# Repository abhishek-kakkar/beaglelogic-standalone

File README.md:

# beaglelogic-standalone

BeagleLogic implemented as a turnkey and standalone logic analyzer

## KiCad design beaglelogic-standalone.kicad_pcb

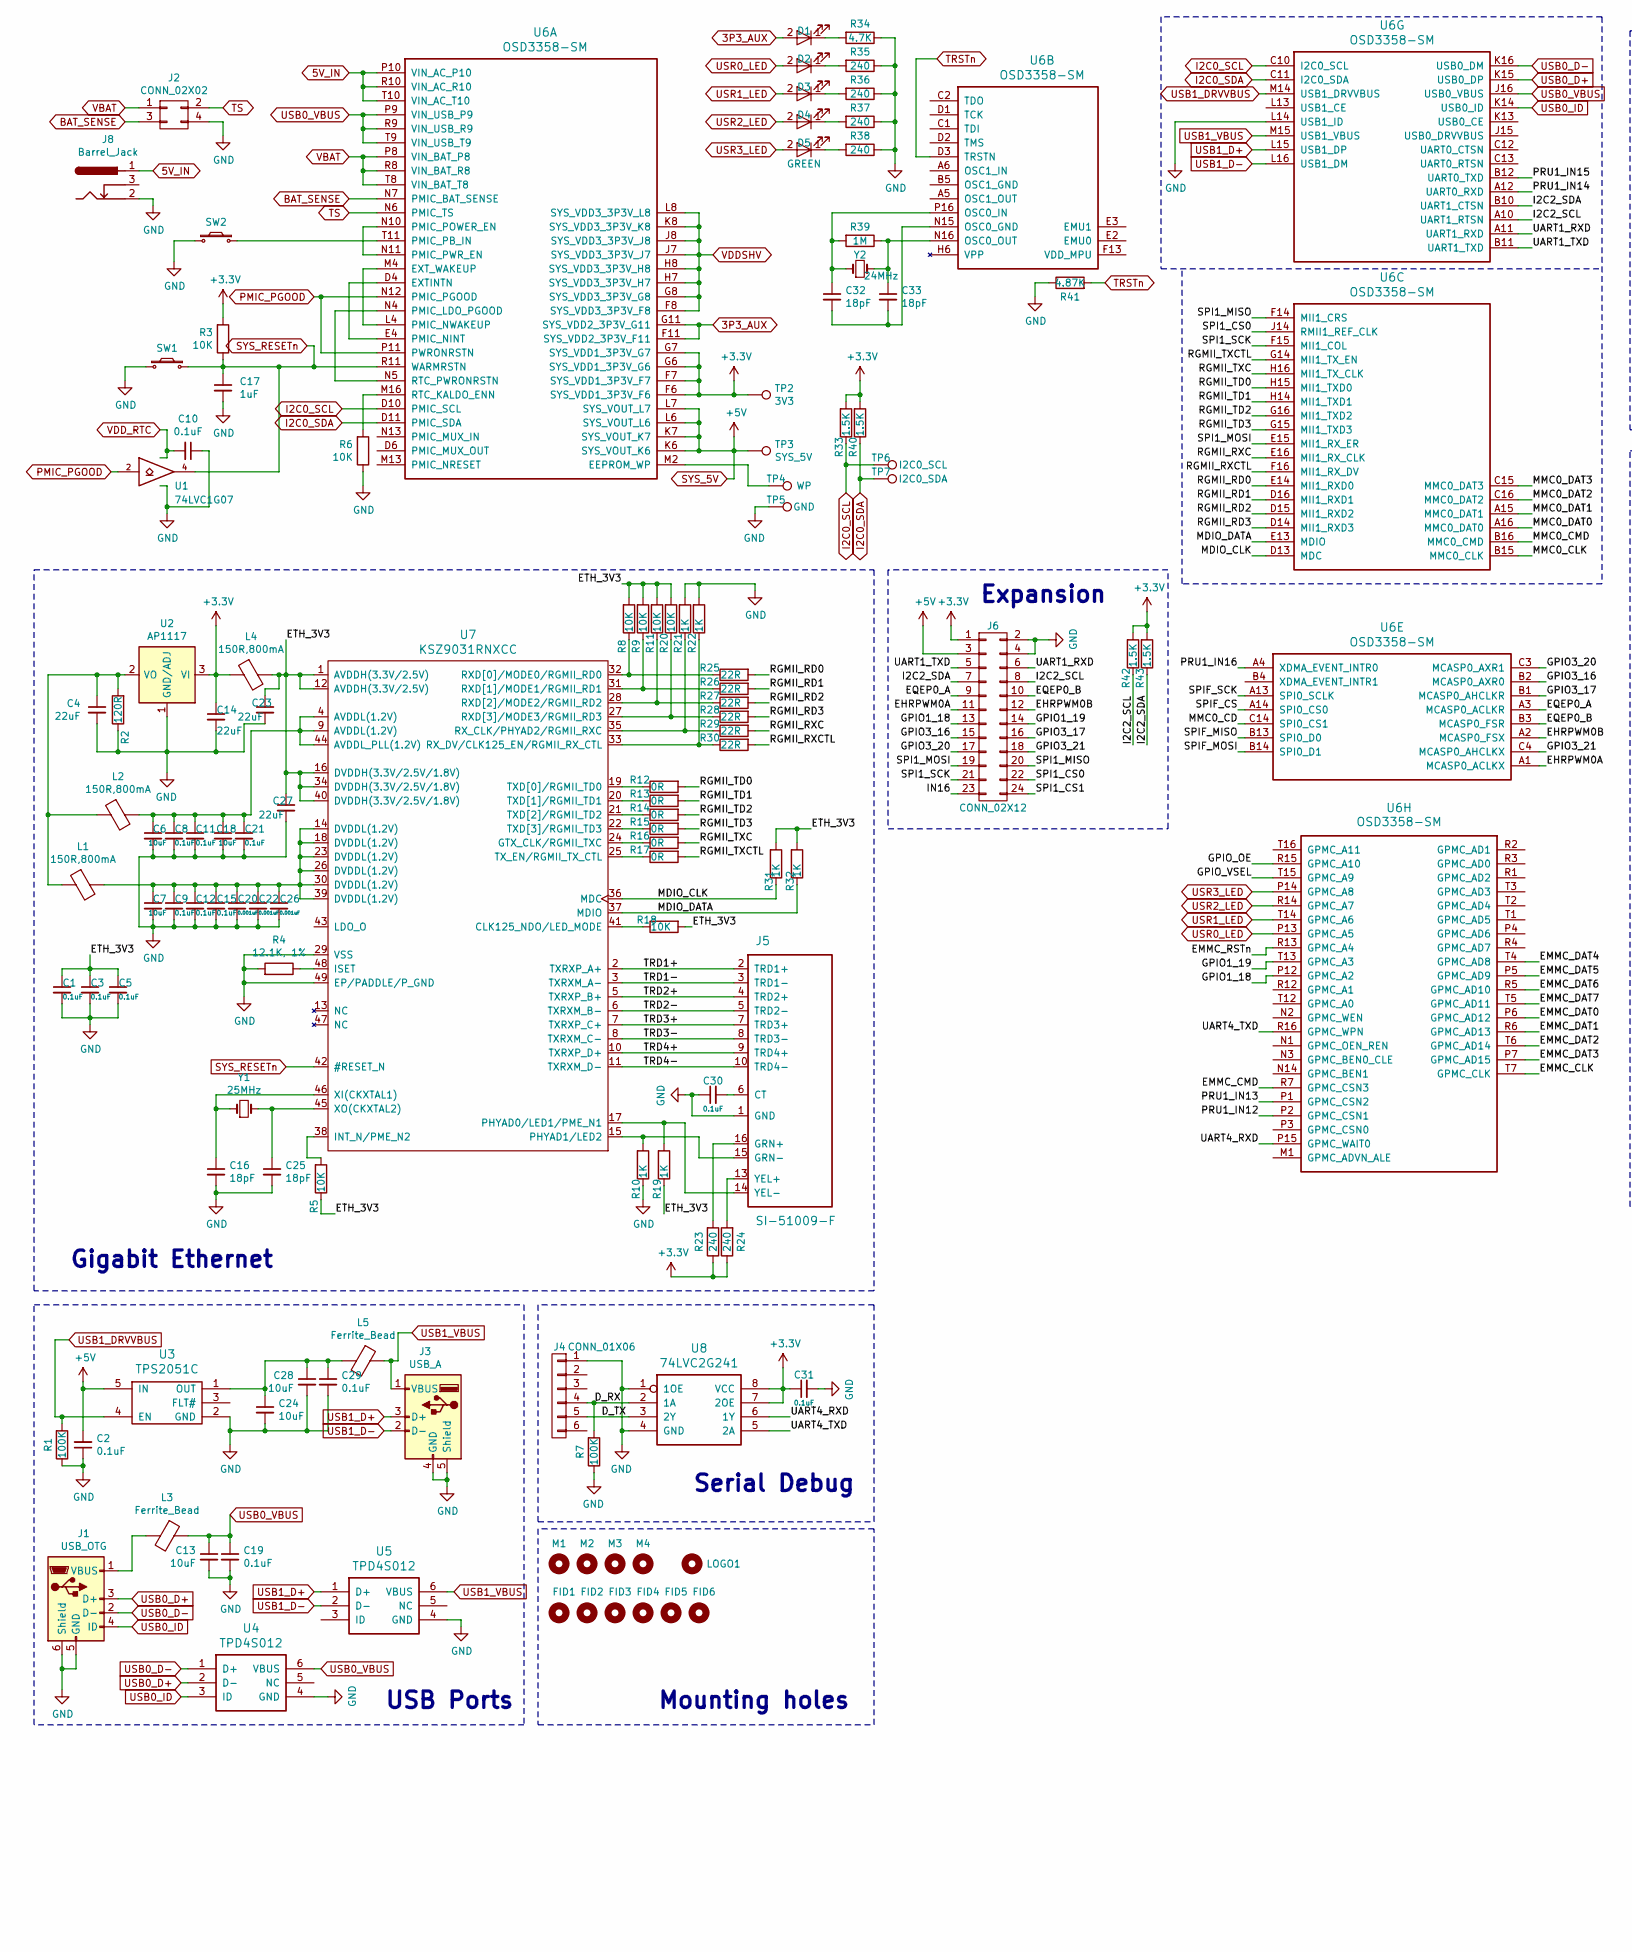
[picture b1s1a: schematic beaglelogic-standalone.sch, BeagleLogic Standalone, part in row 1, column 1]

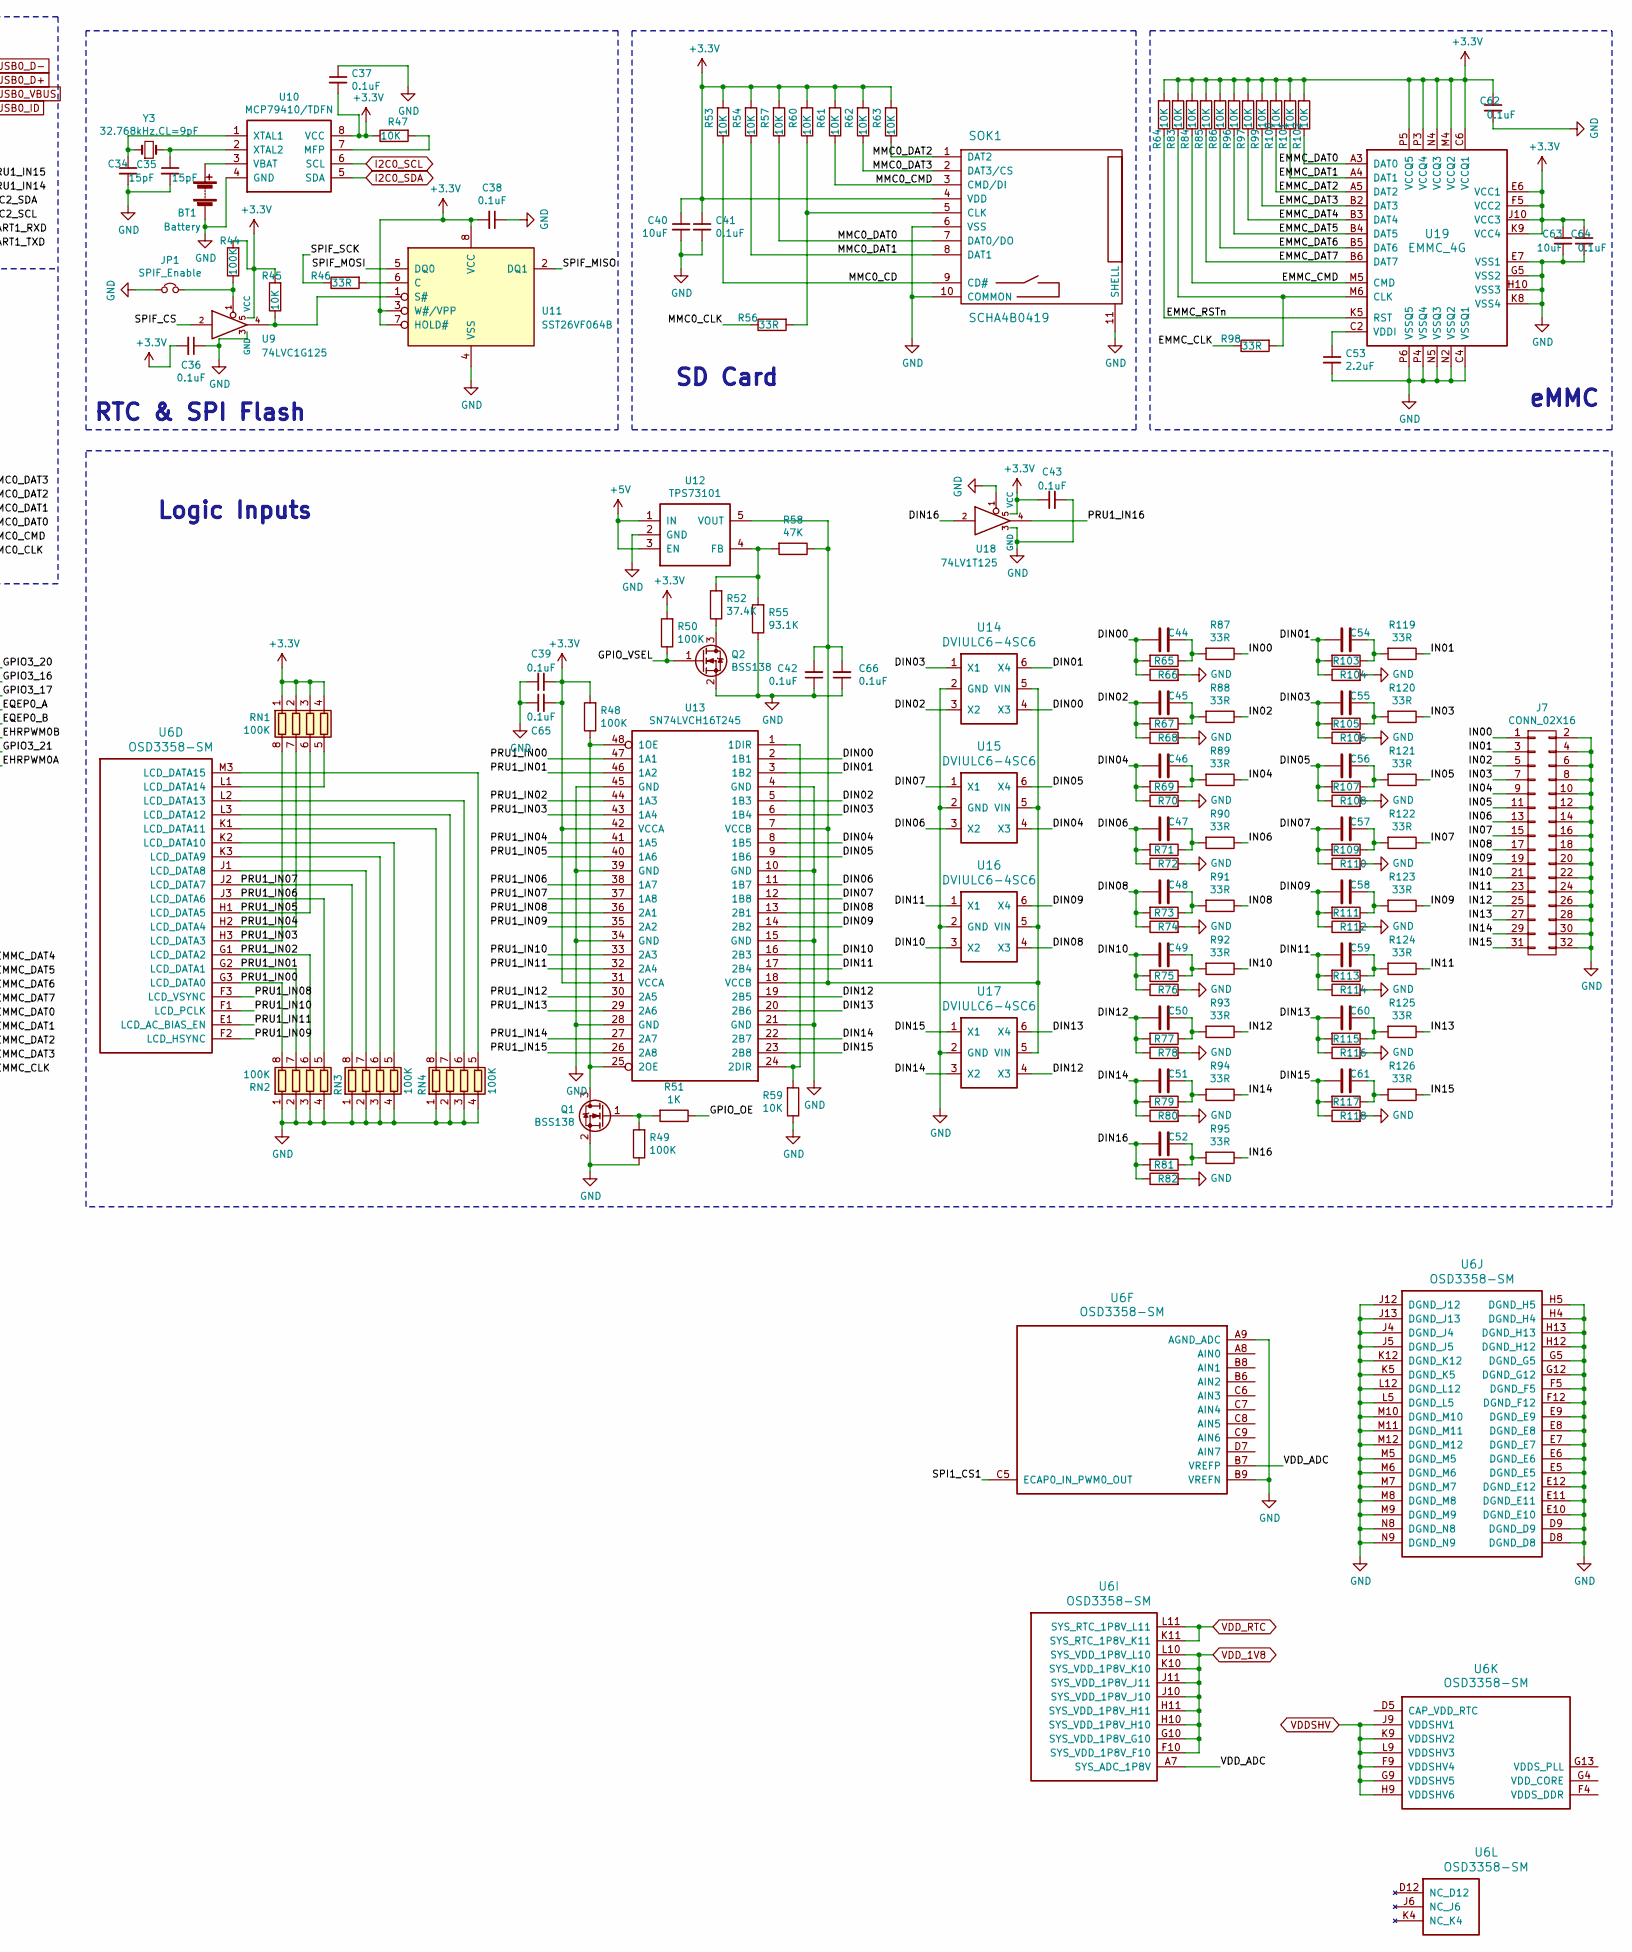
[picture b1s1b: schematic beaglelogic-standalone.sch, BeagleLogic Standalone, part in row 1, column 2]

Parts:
BT1: Battery; Test_Point_2Pads
C1, C2, C3, C5, C8, C9, C10, C11, C12, C15, C19, C21, C29, C30, C31, C36, C37, C38, C39, C41, C42, C43, C62, C64, C65, C66: 0.1uF; C_0402
C4, C14, C23, C27: 22uF; C_0603
C6, C7, C13, C18, C24, C28, C40, C63: 10uF; C_0603
C16, C25, C32, C33: 18pF; C_0402
C17: 1uF; C_0402
C20, C22, C26: 0.001uF; C_0402
C34, C35: 15pF; C_0402
C44, C45, C46, C47, C48, C49, C50, C51, C52, C54, C55, C56, C57, C58, C59, C60, C61: 1pF, DNI; C_0402
C53: 2.2uF; C_0402
D1, D2, D3, D4, D5: GREEN; LED_0603
FID1, FID2, FID3, FID4, FID5, FID6: Mounting_Hole; Fiducial_1mm_Dia_2.54mm_Outer_CopperTop
J1: USB_OTG; 10118192-0001LF
J2: CONN_02X02; Pin_Header_Straight_2x02_Pitch2.54mm
J3: USB_A
J4: CONN_01X06; Pin_Header_Straight_1x06_Pitch2.54mm
J5: SI-51009-F
J6: CONN_02X12; Pin_Header_Angled_2x12_Pitch2.54mm_reversed
J7: CONN_02X16; Pin_Header_Angled_2x16_Pitch2.54mm
J8: Barrel_Jack; BARREL_JACK
JP1: SPIF_Enable; Test_Point_2Pads
L1, L2, L4: 150R,800mA; R_0603
L3, L5: Ferrite_Bead; R_0603
LOGO1: TEST_1P; beaglelogic-logo
M1, M2, M3, M4: TEST_1P; MountingHole_3.2mm_M3
Q1, Q2: BSS138; SOT-23
R1, R7, R44, R48, R49, R50: 100K; R_0402
R2: 120R; R_0603
R3, R5, R6, R8, R9, R11, R18, R20, R45, R47, R53, R54, R57, R59, R60, R61, R62, R63, R64, R83, R84, R85, R86, R96, R97, R99, R100, R101, R102: 10K; R_0402
R4: 12.1K, 1%; R_0402
R10, R19, R21, R22, R31, R32, R51: 1K; R_0402
R12, R13, R14, R15, R16, R17: 0R; R_0402
R23, R24, R35, R36, R37, R38: 240; R_0402
R25, R26, R27, R28, R29, R30: 22R; R_0402
R33, R40, R42, R43: 1.5K; R_0402
R34: 4.7K; R_0402
R39: 1M; R_0402
R41: 4.87K; R_0402
R46, R56, R87, R88, R89, R90, R91, R92, R93, R94, R95, R98, R119, R120, R121, R122, R123, R124, R125, R126: 33R; R_0402
R52: 37.4K; R_0402
R55: 93.1K; R_0402
R58: 47K; R_0402
R65, R67, R69, R71, R73, R75, R77, R79, R81, R103, R105, R107, R109, R111, R113, R115, R117: 100K,SH; R_0402
R66, R68, R70, R72, R74, R76, R78, R80, R82, R104, R106, R108, R110, R112, R114, R116, R118: 1M,S; R_0402
RN1, RN2, RN3, RN4: 100K; R_Array_Concave_4x0402
SOK1: SCHA4B0419
SW1, SW2: SW_PUSH_SMALL_H; SW_SPST_EVQPE1
TP2: 3V3; Measurement_Point_Round-SMD-Pad_Small
TP3: SYS_5V; Measurement_Point_Round-SMD-Pad_Small
TP4: WP; Measurement_Point_Round-SMD-Pad_Small
TP5: GND; Measurement_Point_Round-SMD-Pad_Small
TP6: I2C0_SCL; Measurement_Point_Round-SMD-Pad_Small
TP7: I2C0_SDA; Measurement_Point_Round-SMD-Pad_Small
U1: 74LVC1G07; SOT-353_SC-70-5
U2: AP1117; SOT-223
U3: TPS2051C; SOT-23-5
U4, U5: TPD4S012; DRY
U6: OSD3358-SM; BGA-256-1-27mm
U7: KSZ9031RNXCC; QFN-48-1EP_7x7mm
U8: 74LVC2G241; VSSOP-8_2.4x2.1mm_Pitch0.5mm
U9: 74LVC1G125; SOT-353_SC-70-5
U10: MCP79410/TDFN; DFN-8-1EP_3x2mm
U11: SST26VF064B; SOIJ-8_5.3x5.3mm_Pitch1.27mm
U12: TPS73101; SOT-23-5
U13: SN74LVCH16T245; TSSOP-48_6.1x12.5mm_Pitch0.5mm
U14, U15, U16, U17: DVIULC6-4SC6; SOT-23-6
U18: 74LV1T125; SOT-353_SC-70-5
U19: EMMC_4G; BGA153N50P14X14_1150X1300X100
Y1: 25MHz; Crystal_SMD_5032-2pin_5.0x3.2mm
Y2: 24MHz; Crystal_SMD_5032-2pin_5.0x3.2mm
Y3: 32.768kHz,CL=9pF; Crystal_SMD_3215-2pin_3.2x1.5mm

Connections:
3P3_AUX: D1.2 (A), U6.F11 (SYS_VDD2_3P3V_F11), U6.G11 (SYS_VDD2_3P3V_G11)
5V_IN: J8.1, U6.P10 (VIN_AC_P10), U6.R10 (VIN_AC_R10), U6.T10 (VIN_AC_T10)
+3V3: C14.1, C31.1, C36.2, C37.2, C38.2, C39.2, C40.1, C41.1, C43.1, C62.1, C63.1, C64.1, C65.2, J6.1, L4.1, R3.2, R23.1, R24.1, R33.2, R40.2, R42.2, R43.2, R44.2, R45.2, R47.1, R48.2, R50.2, R53.2, R54.2, R57.2, R60.2, R61.2, R62.2, R63.2, R64.2, R83.2, R84.2, R85.2, R86.2, R96.2, R97.2, R99.2, R100.2, R101.2, R102.2, RN1.1 (R1.1), RN1.2 (R2.1), RN1.3 (R3.1), RN1.4 (R4.1), SOK1.4 (VDD), TP2.1, U2.3 (VI), U6.F6 (SYS_VDD1_3P3V_F6), U6.F7 (SYS_VDD1_3P3V_F7), U6.G6 (SYS_VDD1_3P3V_G6), U6.G7 (SYS_VDD1_3P3V_G7), U8.7 (2OE), U8.8 (VCC), U9.5 (VCC), U10.8 (VCC), U11.3 (W#/VPP), U11.7 (HOLD#), U11.8 (VCC), U13.31 (VCCA), U13.42 (VCCA), U18.5 (VCC), U19.C6 (VCCQ1), U19.E6 (VCC1), U19.F5 (VCC2), U19.J10 (VCC3), U19.K9 (VCC4), U19.M4 (VCCQ2), U19.N4 (VCCQ3), U19.P3 (VCCQ4), U19.P5 (VCCQ5)
/DIN00: C44.2, R65.2, R66.1, U13.2 (1B1), U14.4 (X3)
/DIN01: C54.2, R103.2, R104.1, U13.3 (1B2), U14.6 (X4)
/DIN02: C45.2, R67.2, R68.1, U13.5 (1B3), U14.3 (X2)
/DIN03: C55.2, R105.2, R106.1, U13.6 (1B4), U14.1 (X1)
/DIN04: C46.2, R69.2, R70.1, U13.8 (1B5), U15.4 (X3)
/DIN05: C56.2, R107.2, R108.1, U13.9 (1B6), U15.6 (X4)
/DIN06: C47.2, R71.2, R72.1, U13.11 (1B7), U15.3 (X2)
/DIN07: C57.2, R109.2, R110.1, U13.12 (1B8), U15.1 (X1)
/DIN08: C48.2, R73.2, R74.1, U13.13 (2B1), U16.4 (X3)
/DIN09: C58.2, R111.2, R112.1, U13.14 (2B2), U16.6 (X4)
/DIN10: C49.2, R75.2, R76.1, U13.16 (2B3), U16.3 (X2)
/DIN11: C59.2, R113.2, R114.1, U13.17 (2B4), U16.1 (X1)
/DIN12: C50.2, R77.2, R78.1, U13.19 (2B5), U17.4 (X3)
/DIN13: C60.2, R115.2, R116.1, U13.20 (2B6), U17.6 (X4)
/DIN14: C51.2, R79.2, R80.1, U13.22 (2B7), U17.3 (X2)
/DIN15: C61.2, R117.2, R118.1, U13.23 (2B8), U17.1 (X1)
/DIN16: C52.2, R81.2, R82.1, U18.2
/D_RX: J4.4, R7.2, U8.2 (1A)
/D_TX: J4.5, U8.3 (2Y)
/EHRPWM0A: J6.11, U6.A1 (MCASP0_ACLKX)
/EHRPWM0B: J6.12, U6.A2 (MCASP0_FSX)
/EMMC_CLK: R98.1, U6.T7 (GPMC_CLK)
/EMMC_CMD: R84.1, U6.R7 (GPMC_CSN3), U19.M5 (CMD)
/EMMC_DAT0: R102.1, U6.P6 (GPMC_AD12), U19.A3 (DAT0)
/EMMC_DAT1: R101.1, U6.R6 (GPMC_AD13), U19.A4 (DAT1)
/EMMC_DAT2: R100.1, U6.T6 (GPMC_AD14), U19.A5 (DAT2)
/EMMC_DAT3: R99.1, U6.P7 (GPMC_AD15), U19.B2 (DAT3)
/EMMC_DAT4: R97.1, U6.T4 (GPMC_AD8), U19.B3 (DAT4)
/EMMC_DAT5: R96.1, U6.P5 (GPMC_AD9), U19.B4 (DAT5)
/EMMC_DAT6: R86.1, U6.R5 (GPMC_AD10), U19.B5 (DAT6)
/EMMC_DAT7: R85.1, U6.T5 (GPMC_AD11), U19.B6 (DAT7)
/EMMC_RSTn: R64.1, U6.R13 (GPMC_A4), U19.K5 (RST)
/EQEP0_A: J6.9, U6.A3 (MCASP0_ACLKR)
/EQEP0_B: J6.10, U6.B3 (MCASP0_FSR)
/ETH_3V3: C1.1, C3.1, C5.1, C23.1, C27.1, L4.2, R5.1, R8.2, R9.2, R11.2, R18.2, R19.1, R20.2, R31.2, R32.2, U7.1 (AVDDH(3.3V/2.5V)), U7.12 (AVDDH(3.3V/2.5V)), U7.16 (DVDDH(3.3V/2.5V/1.8V)), U7.34 (DVDDH(3.3V/2.5V/1.8V)), U7.40 (DVDDH(3.3V/2.5V/1.8V))
/GPIO1_18: J6.13, U6.P12 (GPMC_A2)
/GPIO1_19: J6.14, U6.T13 (GPMC_A3)
/GPIO3_16: J6.15, U6.B2 (MCASP0_AXR0)
/GPIO3_17: J6.16, U6.B1 (MCASP0_AHCLKR)
/GPIO3_20: J6.17, U6.C3 (MCASP0_AXR1)
/GPIO3_21: J6.18, U6.C4 (MCASP0_AHCLKX)
/GPIO_OE: R51.1, U6.R15 (GPMC_A10)
/GPIO_VSEL: Q2.1 (G), R50.1, U6.T15 (GPMC_A9)
/I2C2_SCL: J6.8, R42.1, U6.A10 (UART1_RTSN)
/I2C2_SDA: J6.7, R43.1, U6.B10 (UART1_CTSN)
/IN00: J7.1, R87.1
/IN01: J7.3, R119.1
/IN02: J7.5, R88.1
/IN03: J7.7, R120.1
/IN04: J7.9, R89.1
/IN05: J7.11, R121.1
/IN06: J7.13, R90.1
/IN07: J7.15, R122.1
/IN08: J7.17, R91.1
/IN09: J7.19, R123.1
/IN10: J7.21, R92.1
/IN11: J7.23, R124.1
/IN12: J7.25, R93.1
/IN13: J7.27, R125.1
/IN14: J7.29, R94.1
/IN15: J7.31, R126.1
/IN16: J6.23, R95.1
/MDIO_CLK: R31.1, U6.D13 (MDC), U7.36 (MDC)
/MDIO_DATA: R32.1, U6.E13 (MDIO), U7.37 (MDIO)
/MMC0_CD: R53.1, SOK1.9 (CD#), U6.C14 (SPI0_CS1)
/MMC0_CLK: R56.1, U6.B15 (MMC0_CLK)
/MMC0_CMD: R61.1, SOK1.3 (CMD/DI), U6.B16 (MMC0_CMD)
/MMC0_DAT0: R57.1, SOK1.7 (DAT0/DO), U6.A16 (MMC0_DAT0)
/MMC0_DAT1: R54.1, SOK1.8 (DAT1), U6.A15 (MMC0_DAT1)
/MMC0_DAT2: R63.1, SOK1.1 (DAT2), U6.C16 (MMC0_DAT2)
/MMC0_DAT3: R62.1, SOK1.2 (DAT3/CS), U6.C15 (MMC0_DAT3)
/PRU1_IN00: RN2.8 (R1.2), U6.G3 (LCD_DATA0), U13.47 (1A1)
/PRU1_IN01: RN2.7 (R2.2), U6.G2 (LCD_DATA1), U13.46 (1A2)
/PRU1_IN02: RN2.6 (R3.2), U6.G1 (LCD_DATA2), U13.44 (1A3)
/PRU1_IN03: RN1.8 (R1.2), U6.H3 (LCD_DATA3), U13.43 (1A4)
/PRU1_IN04: RN1.7 (R2.2), U6.H2 (LCD_DATA4), U13.41 (1A5)
/PRU1_IN05: RN1.6 (R3.2), U6.H1 (LCD_DATA5), U13.40 (1A6)
/PRU1_IN06: RN2.5 (R4.2), U6.J3 (LCD_DATA6), U13.38 (1A7)
/PRU1_IN07: RN3.8 (R1.2), U6.J2 (LCD_DATA7), U13.37 (1A8)
/PRU1_IN08: U6.F3 (LCD_VSYNC), U13.36 (2A1)
/PRU1_IN09: U6.F2 (LCD_HSYNC), U13.35 (2A2)
/PRU1_IN10: U6.F1 (LCD_PCLK), U13.33 (2A3)
/PRU1_IN11: U6.E1 (LCD_AC_BIAS_EN), U13.32 (2A4)
/PRU1_IN12: U6.P2 (GPMC_CSN1), U13.30 (2A5)
/PRU1_IN13: U6.P1 (GPMC_CSN2), U13.29 (2A6)
/PRU1_IN14: U6.A12 (UART0_RXD), U13.27 (2A7)
/PRU1_IN15: U6.B12 (UART0_TXD), U13.26 (2A8)
/PRU1_IN16: U6.A4 (XDMA_EVENT_INTR0), U18.4
/RGMII_RD0: R25.2, U6.E14 (MII1_RXD0)
/RGMII_RD1: R26.2, U6.D16 (MII1_RXD1)
/RGMII_RD2: R27.2, U6.D15 (MII1_RXD2)
/RGMII_RD3: R28.2, U6.D14 (MII1_RXD3)
/RGMII_RXC: R29.2, U6.E16 (MII1_RX_CLK)
/RGMII_RXCTL: R30.2, U6.F16 (MII1_RX_DV)
/RGMII_TD0: R12.2, U6.H15 (MII1_TXD0)
/RGMII_TD1: R13.2, U6.H14 (MII1_TXD1)
/RGMII_TD2: R14.2, U6.G16 (MII1_TXD2)
/RGMII_TD3: R15.2, U6.G15 (MII1_TXD3)
/RGMII_TXC: R16.2, U6.H16 (MII1_TX_CLK)
/RGMII_TXCTL: R17.2, U6.G14 (MII1_TX_EN)
/SPI1_CS0: J6.22, U6.J14 (RMII1_REF_CLK)
/SPI1_CS1: J6.24, U6.C5 (ECAP0_IN_PWM0_OUT)
/SPI1_MISO: J6.20, U6.F14 (MII1_CRS)
/SPI1_MOSI: J6.19, U6.E15 (MII1_RX_ER)
/SPI1_SCK: J6.21, U6.F15 (MII1_COL)
/SPIF_CS: U6.A14 (SPI0_CS0), U9.2
/SPIF_MISO: U6.B13 (SPI0_D0), U11.2 (DQ1)
/SPIF_MOSI: U6.B14 (SPI0_D1), U11.5 (DQ0)
/SPIF_SCK: R46.1, U6.A13 (SPI0_SCLK)
/TRD1+: J5.2 (TRD1+), U7.2 (TXRXP_A+)
/TRD1-: J5.3 (TRD1-), U7.3 (TXRXM_A-)
/TRD2+: J5.4 (TRD2+), U7.5 (TXRXP_B+)
/TRD2-: J5.5 (TRD2-), U7.6 (TXRXM_B-)
/TRD3+: J5.7 (TRD3+), U7.7 (TXRXP_C+)
/TRD3-: J5.8 (TRD3-), U7.8 (TXRXM_C-)
/TRD4+: J5.9 (TRD4+), U7.10 (TXRXP_D+)
/TRD4-: J5.10 (TRD4-), U7.11 (TXRXM_D-)
/UART1_RXD: J6.6, U6.A11 (UART1_RXD)
/UART1_TXD: J6.5, U6.B11 (UART1_TXD)
/UART4_RXD: U6.P15 (GPMC_WAIT0), U8.6 (1Y)
/UART4_TXD: U6.R16 (GPMC_WPN), U8.5 (2A)
/VDD_ADC: U6.A7 (SYS_ADC_1P8V), U6.B7 (VREFP)
BAT_SENSE: J2.3, U6.N7 (PMIC_BAT_SENSE)
GND: BT1.2 (-), C1.2, C2.1, C3.2, C4.2, C5.2, C6.2, C7.2, C8.2, C9.2, C10.1, C11.2, C12.2, C13.2, C14.2, C15.2, C16.2, C17.2, C18.2, C19.2, C20.2, C21.2, C22.2, C23.2, C24.2, C25.2, C26.2, C27.2, C28.2, C29.2, C30.1, C31.2, C34.2, C35.2, C36.1, C37.1, C38.1, C39.1, C40.2, C41.2, C42.1, C43.2, C53.2, C62.2, C63.2, C64.2, C65.1, C66.1, J1.5 (GND), J1.6 (Shield), J2.4, J3.4 (GND), J3.5 (Shield), J4.1, J5.1 (GND), J6.2, J6.4, J7.2, J7.4, J7.6, J7.8, J7.10, J7.12, J7.14, J7.16, J7.18, J7.20, J7.22, J7.24, J7.26, J7.28, J7.30, J7.32, J8.2, JP1.1, Q1.2 (S), Q2.2 (S), R1.1, R2.1, R4.2, R6.1, R7.1, R10.1, R21.2, R22.2, R34.1, R35.1, R36.1, R37.1, R38.1, R41.1, R49.1, R55.1, R59.1, R66.2, R68.2, R70.2, R72.2, R74.2, R76.2, R78.2, R80.2, R82.2, R104.2, R106.2, R108.2, R110.2, R112.2, R114.2, R116.2, R118.2, RN2.1 (R1.1), RN2.2 (R2.1), RN2.3 (R3.1), RN2.4 (R4.1), RN3.1 (R1.1), RN3.2 (R2.1), RN3.3 (R3.1), RN3.4 (R4.1), RN4.1 (R1.1), RN4.2 (R2.1), RN4.3 (R3.1), RN4.4 (R4.1), SOK1.6 (VSS), SOK1.10 (COMMON), SOK1.11 (SHELL), SW1.1, SW2.1, TP5.1, U1.3 (GND), U2.1 (GND/ADJ), U3.2 (GND), U4.4 (GND), U5.4 (GND), U6.A9 (AGND_ADC), U6.B9 (VREFN), U6.D8 (DGND_D8), U6.D9 (DGND_D9), U6.E5 (DGND_E5), U6.E6 (DGND_E6), U6.E7 (DGND_E7), U6.E8 (DGND_E8), U6.E9 (DGND_E9), U6.E10 (DGND_E10), U6.E11 (DGND_E11), U6.E12 (DGND_E12), U6.F5 (DGND_F5), U6.F12 (DGND_F12), U6.G5 (DGND_G5), U6.G12 (DGND_G12), U6.H4 (DGND_H4), U6.H5 (DGND_H5), U6.H12 (DGND_H12), U6.H13 (DGND_H13), U6.J4 (DGND_J4), U6.J5 (DGND_J5), U6.J12 (DGND_J12), U6.J13 (DGND_J13), U6.K5 (DGND_K5), U6.K12 (DGND_K12), U6.L5 (DGND_L5), U6.L12 (DGND_L12), U6.L14 (USB1_ID), U6.M5 (DGND_M5), U6.M6 (DGND_M6), U6.M7 (DGND_M7), U6.M8 (DGND_M8), U6.M9 (DGND_M9), U6.M10 (DGND_M10), U6.M11 (DGND_M11), U6.M12 (DGND_M12), U6.N8 (DGND_N8), U6.N9 (DGND_N9), U7.29 (VSS), U7.49 (EP/PADDLE/P_GND), U8.1 (1OE), U8.4 (GND), U9.3 (GND), U10.4 (GND), U11.4 (VSS), U12.2 (GND), U13.4 (GND), U13.10 (GND), U13.15 (GND), U13.21 (GND), U13.28 (GND), U13.34 (GND), U13.39 (GND), U13.45 (GND), U14.2 (GND), U15.2 (GND), U16.2 (GND), U17.2 (GND), U18.1, U18.3 (GND), U19.C4 (VSSQ1), U19.E7 (VSS1), U19.G5 (VSS2), U19.H10 (VSS3), U19.K8 (VSS4), U19.N2 (VSSQ2), U19.N5 (VSSQ3), U19.P4 (VSSQ4), U19.P6 (VSSQ5)
I2C0_SCL: R33.1, TP6.1, U6.C10 (I2C0_SCL), U6.D10 (PMIC_SCL), U10.6 (SCL)
I2C0_SDA: R40.1, TP7.1, U6.C11 (I2C0_SDA), U6.D11 (PMIC_SDA), U10.5 (SDA)
unnamed: BT1.1 (+), U10.3 (VBAT)
unnamed: C4.1, L1.1, L2.1, R2.2, U2.2 (VO), U2.4 (VO)
unnamed: C6.1, C8.1, C11.1, C18.1, C21.1, L2.2, U7.4 (AVDDL(1.2V)), U7.9 (AVDDL(1.2V)), U7.44 (AVDDL_PLL(1.2V))
unnamed: C7.1, C9.1, C12.1, C15.1, C20.1, C22.1, C26.1, L1.2, U7.14 (DVDDL(1.2V)), U7.18 (DVDDL(1.2V)), U7.23 (DVDDL(1.2V)), U7.26 (DVDDL(1.2V)), U7.30 (DVDDL(1.2V)), U7.39 (DVDDL(1.2V))
unnamed: C16.1, U7.46 (XI(CKXTAL1)), Y1.1
unnamed: C24.1, C28.1, C29.1, L5.2, U3.1 (OUT)
unnamed: C25.1, U7.45 (XO(CKXTAL2)), Y1.2
unnamed: C30.2, J5.6 (CT)
unnamed: C32.1, R39.2, U6.P16 (OSC0_IN), Y2.1
unnamed: C32.2, C33.2, U6.N15 (OSC0_GND)
unnamed: C33.1, R39.1, U6.N16 (OSC0_OUT), Y2.2
unnamed: C34.1, U10.1 (XTAL1), Y3.1
unnamed: C35.1, U10.2 (XTAL2), Y3.2
unnamed: C42.2, C66.2, R58.1, U12.5 (VOUT), U13.7 (VCCB), U13.18 (VCCB), U14.5 (VIN), U15.5 (VIN), U16.5 (VIN), U17.5 (VIN)
unnamed: C44.1, R65.1, R87.2
unnamed: C45.1, R67.1, R88.2
unnamed: C46.1, R69.1, R89.2
unnamed: C47.1, R71.1, R90.2
unnamed: C48.1, R73.1, R91.2
unnamed: C49.1, R75.1, R92.2
unnamed: C50.1, R77.1, R93.2
unnamed: C51.1, R79.1, R94.2
unnamed: C52.1, R81.1, R95.2
unnamed: C53.1, U19.C2 (VDDI)
unnamed: C54.1, R103.1, R119.2
unnamed: C55.1, R105.1, R120.2
unnamed: C56.1, R107.1, R121.2
unnamed: C57.1, R109.1, R122.2
unnamed: C58.1, R111.1, R123.2
unnamed: C59.1, R113.1, R124.2
unnamed: C60.1, R115.1, R125.2
unnamed: C61.1, R117.1, R126.2
unnamed: D1.1 (K), R34.2
unnamed: D2.1 (K), R35.2
unnamed: D3.1 (K), R36.2
unnamed: D4.1 (K), R37.2
unnamed: D5.1 (K), R38.2
unnamed: J1.1 (VBUS), L3.2
unnamed: J5.13 (YEL+), R24.2
unnamed: J5.14 (YEL-), R19.2, U7.17 (PHYAD0/LED1/PME_N1)
unnamed: J5.15 (GRN-), R10.2, U7.15 (PHYAD1/LED2)
unnamed: J5.16 (GRN+), R23.2
unnamed: JP1.2, R44.1, U9.1
unnamed: Q1.1 (G), R49.2, R51.2
unnamed: Q1.3 (D), R48.1, U13.25 (2OE), U13.48 (1OE)
unnamed: Q2.3 (D), R52.1
unnamed: R4.1, U7.48 (ISET)
unnamed: R5.2, U7.38 (INT_N/PME_N2)
unnamed: R6.2, U6.M16 (RTC_KALDO_ENN)
unnamed: R11.1, R27.1, U7.28 (RXD[2]/MODE2/RGMII_RD2)
unnamed: R12.1, U7.19 (TXD[0]/RGMII_TD0)
unnamed: R13.1, U7.20 (TXD[1]/RGMII_TD1)
unnamed: R14.1, U7.21 (TXD[2]/RGMII_TD2)
unnamed: R15.1, U7.22 (TXD[3]/RGMII_TD3)
unnamed: R16.1, U7.24 (GTX_CLK/RGMII_TXC)
unnamed: R17.1, U7.25 (TX_EN/RGMII_TX_CTL)
unnamed: R18.1, U7.41 (CLK125_NDO/LED_MODE)
unnamed: R20.1, R28.1, U7.27 (RXD[3]/MODE3/RGMII_RD3)
unnamed: R21.1, R29.1, U7.35 (RX_CLK/PHYAD2/RGMII_RXC)
unnamed: R22.1, R30.1, U7.33 (RX_DV/CLK125_EN/RGMII_RX_CTL)
unnamed: R8.1, R25.1, U7.32 (RXD[0]/MODE0/RGMII_RD0)
unnamed: R9.1, R26.1, U7.31 (RXD[1]/MODE1/RGMII_RD1)
unnamed: R45.1, U9.4, U11.1 (S#)
unnamed: R46.2, U11.6 (C)
unnamed: R47.2, U10.7 (MFP)
unnamed: R52.2, R55.2, R58.2, U12.4 (FB)
unnamed: R56.2, R60.1, SOK1.5 (CLK)
unnamed: R59.2, U13.1 (1DIR), U13.24 (2DIR)
unnamed: R83.1, R98.2, U19.M6 (CLK)
unnamed: RN1.5 (R4.2), U6.L1 (LCD_DATA14)
unnamed: RN3.5 (R4.2), U6.K2 (LCD_DATA10)
unnamed: RN3.6 (R3.2), U6.K3 (LCD_DATA9)
unnamed: RN3.7 (R2.2), U6.J1 (LCD_DATA8)
unnamed: RN4.5 (R4.2), U6.M3 (LCD_DATA15)
unnamed: RN4.6 (R3.2), U6.L2 (LCD_DATA13)
unnamed: RN4.7 (R2.2), U6.L3 (LCD_DATA12)
unnamed: RN4.8 (R1.2), U6.K1 (LCD_DATA11)
unnamed: SW2.2, U6.T11 (PMIC_PB_IN)
unnamed: TP4.1, U6.M2 (EEPROM_WP)
unnamed: U6.D4 (EXTINTN), U6.E4 (PMIC_NINT)
unnamed: U6.L4 (PMIC_NWAKEUP), U6.M4 (EXT_WAKEUP)
unnamed: U6.N4 (PMIC_LDO_PGOOD), U6.N5 (RTC_PWRONRSTN)
unnamed: U6.N10 (PMIC_POWER_EN), U6.N11 (PMIC_PWR_EN)
PMIC_PGOOD: U1.2, U6.N12 (PMIC_PGOOD), U6.P11 (PWRONRSTN)
SYS_5V: C2.2, J6.3, TP3.1, U3.5 (IN), U6.K6 (SYS_VOUT_K6), U6.K7 (SYS_VOUT_K7), U6.L6 (SYS_VOUT_L6), U6.L7 (SYS_VOUT_L7), U12.1 (IN), U12.3 (EN)
SYS_RESETn: C17.1, R3.1, SW1.2, U1.4, U6.R11 (WARMRSTN), U7.42 (#RESET_N)
TRSTn: R41.2, U6.D3 (TRSTN)
TS: J2.2, U6.N6 (PMIC_TS)
USB0_D+: J1.3 (D+), U4.2 (D-), U6.K15 (USB0_DP)
USB0_D-: J1.2 (D-), U4.1 (D+), U6.K16 (USB0_DM)
USB0_ID: J1.4 (ID), U4.3 (ID), U6.K14 (USB0_ID)
USB0_VBUS: C13.1, C19.1, L3.1, U4.6 (VBUS), U6.J16 (USB0_VBUS), U6.P9 (VIN_USB_P9), U6.R9 (VIN_USB_R9), U6.T9 (VIN_USB_T9)
USB1_D+: J3.3 (D+), U5.1 (D+), U6.L15 (USB1_DP)
USB1_D-: J3.2 (D-), U5.2 (D-), U6.L16 (USB1_DM)
USB1_DRVVBUS: R1.2, U3.4 (EN), U6.M14 (USB1_DRVVBUS)
USB1_VBUS: J3.1 (VBUS), L5.1, U5.6 (VBUS), U6.M15 (USB1_VBUS)
USR0_LED: D2.2 (A), U6.P13 (GPMC_A5)
USR1_LED: D3.2 (A), U6.T14 (GPMC_A6)
USR2_LED: D4.2 (A), U6.R14 (GPMC_A7)
USR3_LED: D5.2 (A), U6.P14 (GPMC_A8)
VBAT: J2.1, U6.P8 (VIN_BAT_P8), U6.R8 (VIN_BAT_R8), U6.T8 (VIN_BAT_T8)
VDDSHV: U6.F8 (SYS_VDD3_3P3V_F8), U6.F9 (VDDSHV4), U6.G8 (SYS_VDD3_3P3V_G8), U6.G9 (VDDSHV5), U6.H7 (SYS_VDD3_3P3V_H7), U6.H8 (SYS_VDD3_3P3V_H8), U6.H9 (VDDSHV6), U6.J7 (SYS_VDD3_3P3V_J7), U6.J8 (SYS_VDD3_3P3V_J8), U6.J9 (VDDSHV1), U6.K8 (SYS_VDD3_3P3V_K8), U6.K9 (VDDSHV2), U6.L8 (SYS_VDD3_3P3V_L8), U6.L9 (VDDSHV3)
VDD_1V8: U6.F10 (SYS_VDD_1P8V_F10), U6.G10 (SYS_VDD_1P8V_G10), U6.H10 (SYS_VDD_1P8V_H10), U6.H11 (SYS_VDD_1P8V_H11), U6.J10 (SYS_VDD_1P8V_J10), U6.J11 (SYS_VDD_1P8V_J11), U6.K10 (SYS_VDD_1P8V_K10), U6.L10 (SYS_VDD_1P8V_L10)
VDD_RTC: C10.2, U1.5 (VCC), U6.K11 (SYS_RTC_1P8V_K11), U6.L11 (SYS_RTC_1P8V_L11)

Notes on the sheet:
Gigabit Ethernet
Logic Inputs
SD Card
eMMC
RTC & SPI Flash
USB Ports
Expansion
Serial Debug
Mounting holes

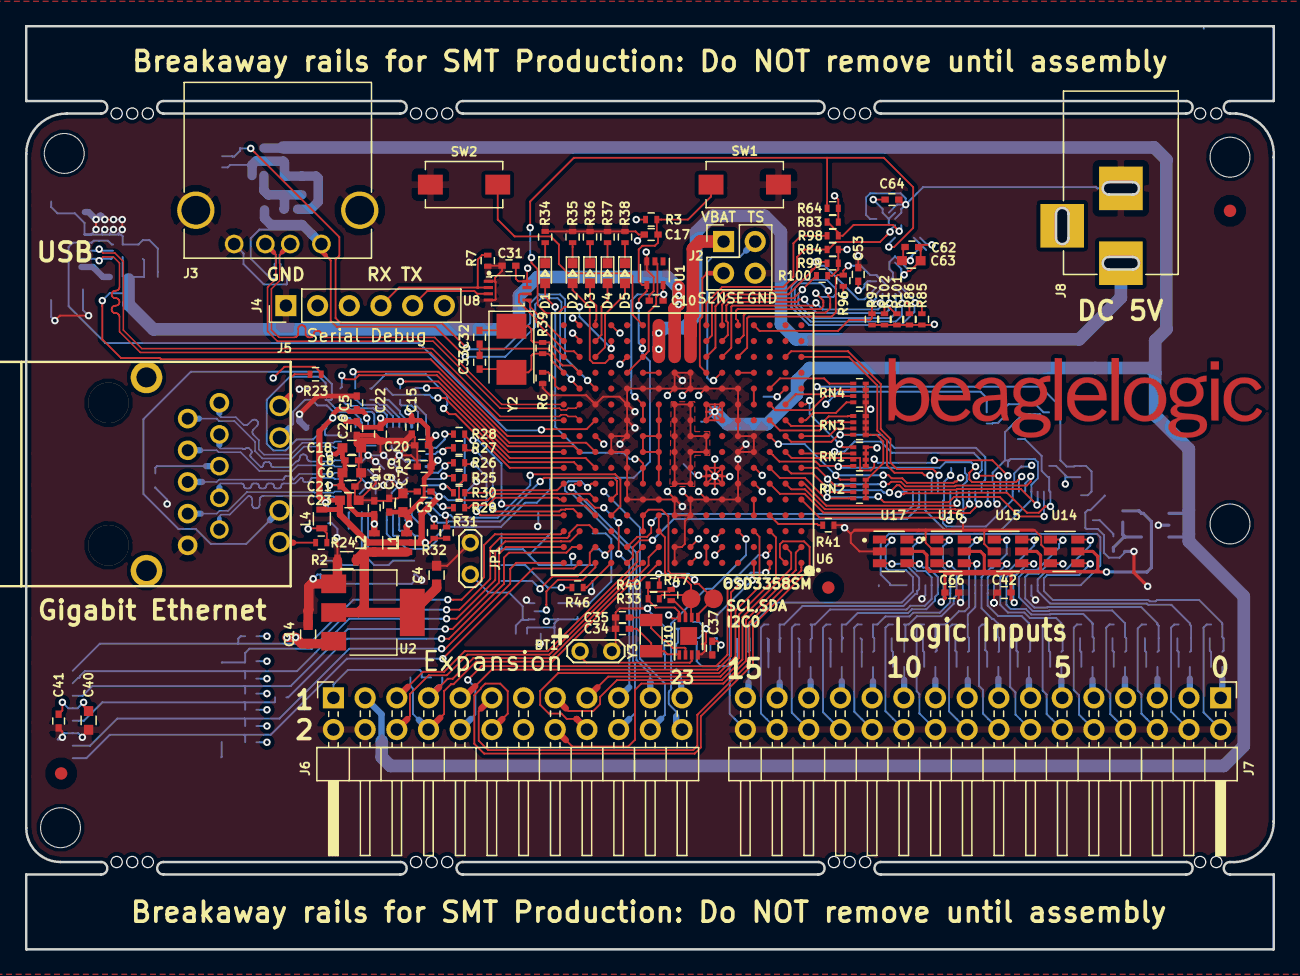
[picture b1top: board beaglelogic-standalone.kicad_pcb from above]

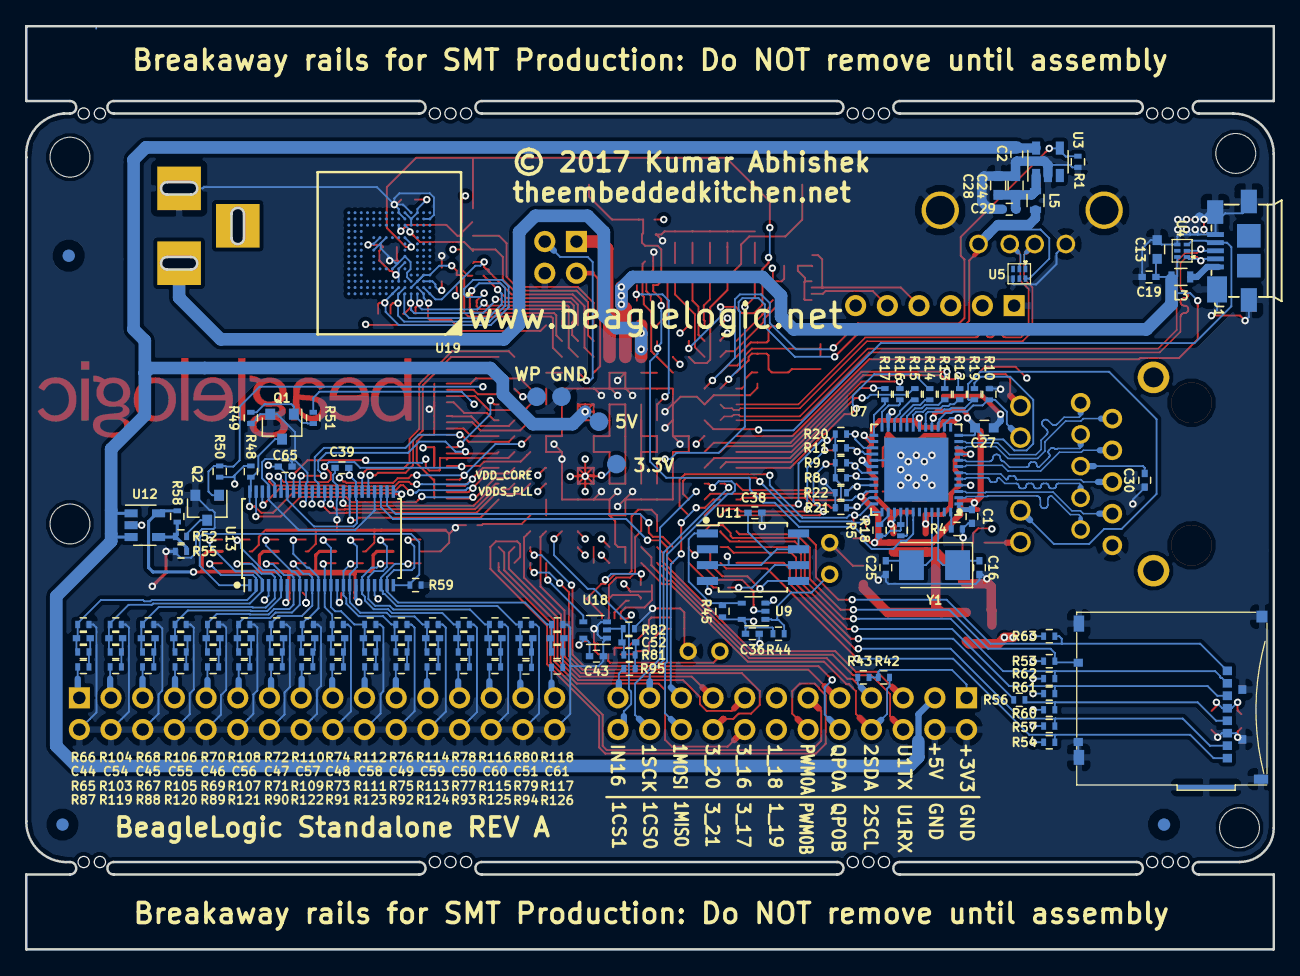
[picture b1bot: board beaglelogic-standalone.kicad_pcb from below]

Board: 4 copper layers, 100.0 x 74.0 mm, 260 parts (146 on the bottom side), 233 nets.

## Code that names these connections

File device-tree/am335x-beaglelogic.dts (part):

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
	i2c0_pins: pinmux_i2c0_pins {
		pinctrl-single,pins = <
			AM33XX_IOPAD(0x988, PIN_INPUT_PULLUP | MUX_MODE0)	/* i2c0_sda.i2c0_sda */
			AM33XX_IOPAD(0x98c, PIN_INPUT_PULLUP | MUX_MODE0)	/* i2c0_scl.i2c0_scl */
		>;
	};

	i2c2_pins: pinmux_i2c2_pins {
		pinctrl-single,pins = <
			AM33XX_IOPAD(0x978, PIN_INPUT_PULLUP | MUX_MODE3)	/* uart1_ctsn.i2c2_sda */
			AM33XX_IOPAD(0x97c, PIN_INPUT_PULLUP | MUX_MODE3)	/* uart1_rtsn.i2c2_scl */
		>;
	};

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	davinci_mdio_default: davinci_mdio_default {
		pinctrl-single,pins = <
			/* MDIO */
			AM33XX_IOPAD(0x948, PIN_INPUT_PULLUP | SLEWCTRL_FAST | MUX_MODE0)	/* mdio_data.mdio_data */
			AM33XX_IOPAD(0x94c, PIN_OUTPUT_PULLUP | MUX_MODE0)			/* mdio_clk.mdio_clk */
		>;
	};

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			0x174 ( PIN_INPUT_PULLDOWN | MUX_MODE6 ) /* (E16) uart0_txd.pr1_pru1_pru_r31[15] */
			0x1b0 ( PIN_INPUT_PULLDOWN | MUX_MODE5 ) /* (A15) xdma_event_intr0.pr1_pru1_pru_r31[16] */

			0x64 ( PIN_OUTPUT | MUX_MODE7 ) /* (U16) gpmc_a9.gpio1[25] - GPIO_VSEL*/
			0x68 ( PIN_OUTPUT | MUX_MODE7 ) /* (T16) gpmc_a10.gpio1[26] - GPIO_OE */
		>;
	};

	uart1_pins: pinmux_uart1_pins {
		pinctrl-single,pins = <
			0x180 ( PIN_INPUT_PULLUP | MUX_MODE0 ) /* (D16) uart1_rxd.uart1_rxd */
			0x184 ( PIN_OUTPUT_PULLDOWN | MUX_MODE0 ) /* (D15) uart1_txd.uart1_txd */
		>;
	};

	uart4_pins: pinmux_uart4_pins {
		pinctrl-single,pins = <
			0x70 ( PIN_INPUT_PULLUP | MUX_MODE6 ) /* (T17) gpmc_wait0.uart4_rxd */
			0x74 ( PIN_OUTPUT_PULLDOWN | MUX_MODE6 ) /* (U17) gpmc_wpn.uart4_txd */
		>;
	};

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			0x108 ( PIN_INPUT_PULLUP | MUX_MODE2 ) /* (H16) gmii1_col.spi1_sclk */
			0x10c ( PIN_INPUT_PULLUP | MUX_MODE2 ) /* (H17) gmii1_crs.spi1_d0 */
			0x110 ( PIN_OUTPUT_PULLUP | MUX_MODE2 ) /* (J15) gmii1_rxer.spi1_d1 */
			0x144 ( PIN_OUTPUT_PULLUP | MUX_MODE2 ) /* (H18) rmii1_refclk.spi1_cs0 */
			0x164 ( PIN_OUTPUT_PULLUP | MUX_MODE2 ) /* (C18) eCAP0_in_PWM0_out.spi1_cs1 */
		>;
	};

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
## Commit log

2017-07-14 Update gitignore
2017-07-14 Schematic Commit - Rev A
2017-07-15 Fix connection to GND of C31
    Was unconnected though appeared connected
2017-07-15 Attach GPIO_OE to its own GPIO instead of SYS_RESETn
2017-07-15 Add jumpered buffer to CS line of SPI Flash
    Suggested change by @mwelling to enable recovery from a board brick.
2017-07-15 Insert series resistors on SPIF SCK, eMMC CLK and SD CLK
2017-07-15 Update to Revision A2
2017-07-16 Add pull-ups on I2C2 lines
2017-07-28 Replace OSD3358 with OSD3358-SM
2017-08-13 Convert to OSD3358-SM: Add missing pins, remove external EEPROM
2017-08-14 Footprint assignment completed
    All footprints assigned.
2017-08-18 Schematic changes... * Flip D0 to D15 and PRU_IN0 to PRU_IN15 for ease in board layout * Switch OSD3358-SM from 400pin BGA to 256pin BGA package
2017-08-18 Flip DP and DM on ESD protector for ease of board layout
2017-08-19 PCB layout: Initial commit
    First pass at component placement.
    Also, slight changes in schematic.
2017-08-19 Add BGA-256 library
2017-08-21 More routing
2017-08-25 Update routing and schematic
2017-09-02 Finalize board outline to 10cm x 6cm
2017-09-04 Route the eMMC
2017-09-04 Route the expansion header
2017-09-05 Almost 90% routed
2017-09-07 Finish routing
2017-09-08 Shrink and add logo
2017-09-09 Final touches to Rev A
    * Shrink logo to fit on board
    * Add fiducials on board
    * Rotate USB-A connector 90 degrees so that it does not interfere with
    microUSB
    * Add helper text
2017-09-10 Add used PCB footprint modules
2017-09-10 Release Candidate
    * Fix incorrect footprint for MCP79410
    * Adjust footprint for KSZ9031 adding more thermal vias in EP and modifying
    paste pattern
    * Add helper text
    * Add vias to some unused signals for testing purposes
2017-09-11 RC2
    * Schematic revision updated to A5
    * Add teardrops to tracks connecting to pin header pads
2017-09-12 Prepare design for production
    * Add breakaway rails on long edges of the PCB as required for prod
    * Remove routing from underneath the ethernet PHY QFN
    * Add triangles to indicate LED polarity on the silkscreen
    * Also add pointers on silkscreen to pin 1 of various ICs
2017-09-12 Prepare for prod: Fix DRC error
2017-09-13 Release PCB rev A1
2017-09-13 Update PCB plotting preferences
2017-10-14 PCB: Update SMD attributes in components
    Needed to generate the Pick-n-Place XY File and ensure all the
    components are there
2017-10-14 Device Tree: Add device tree source for BeagleLogic standalone
2017-10-15 docs: Initial Commit
2017-10-20 Add BeagleLogic standalone image to docs
2017-10-20 docs: Add hardware architecture doc
2017-10-20 docs: Add errata
2017-10-20 docs: Update index.rst with links to new pages
2017-10-21 docs: Add logic_inputs page
2017-10-21 docs: Update Logic Inputs page
2017-10-21 docs: Add expansion connector page
2017-10-21 docs: Update hardware architecture page
2017-10-21 docs: Add acknowledgements page
2017-10-21 docs: Update acknowledgements
2017-10-21 docs: Add prototype pictures
2017-10-21 docs: Add Getting Started page
2017-10-21 docs: Add Troubleshooting page
2017-10-21 docs: Add Technical Specifications page
2017-10-21 docs: Update errata page

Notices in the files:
device-tree/am335x-beaglelogic.dts:
Copyright (C) 2012 Texas Instruments Incorporated - http://www.ti.com
This program is free software; you can redistribute it and/or modify
it under the terms of the GNU General Public License version 2 as
published by the Free Software Foundation.
beaglelogic-standalone.kicad_pcb:
© 2017 Kumar Abhishek
